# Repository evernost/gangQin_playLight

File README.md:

# PlayLight for gangQin
This repository contains the hardware design project for the LED light strip that goes with the gangQin app.

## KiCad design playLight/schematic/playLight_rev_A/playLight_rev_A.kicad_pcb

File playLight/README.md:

# PlayLight for gangQin

Custom piano light design.

---

## Overview

- **Type:** Amplifier
- **Domain:** Analog
- **Status:** Work in progress

---

## Features
TODO

---

## Interfaces

### Inputs
| Name | Type | Range | Description |
|-----|------|-------|-------------|
| IN | Audio | ±1V | Input signal |
| AMP_CV | Analog | 0–5 V | Volume control |

### Outputs
| Name | Type | Description |
|------|------|-------------|
| OUT | Audio | Filtered signal |

---

## Controls

| Control | Type | Description |
|--------|------|-------------|
| Cutoff | Potentiometer | Manual cutoff frequency |
| Resonance | Potentiometer | Feedback amount |

---

## Electrical Characteristics

- **Supply voltage:** ±12V
- **Current consumption:** TBD mA
- **Signal levels:** TBD

---

## Implementation Notes
Section is TODO.

---

## Files

| File | Description |
|-----|-------------|
| `headphones_amp_rev_A.pdf` | Electrical schematic (PDF export)|
| `headphones_amp_rev_A.kicad_pcb` | Schematic (KiCad 9.0.6)|
| `headphones_amp_rev_A.kicad_pcb` | PCB layout (KiCad 9.0.6)|
| `sim/XXX.asc` | SPICE simulation of the Schmitt Trigger |

---

## Calibration / Tuning
None.

---

## Known Issues / TODO
None.

---

## Revision History

| Revision | Date | Notes |
|--------|------|-------|
| Rev A | 2026-04-25 | Initial prototype without MCU |
| Rev B | YYYY-MM-DD | TBD |

---

## Tools
Designed with KiCAD 9.0.7

Designed on a 0.25mm grid (dimensions are driven by standard piano keyboard dimensions, which are in mm)
LED nets routed on a 0.20mm grid to avoid clearance issues when connecting to the LP5036.

---

## Related Modules

Links to other submodules in the repository:
- `../vca/`
- `../ring_modulator/`

---

## References
- TI datasheet: LP5036

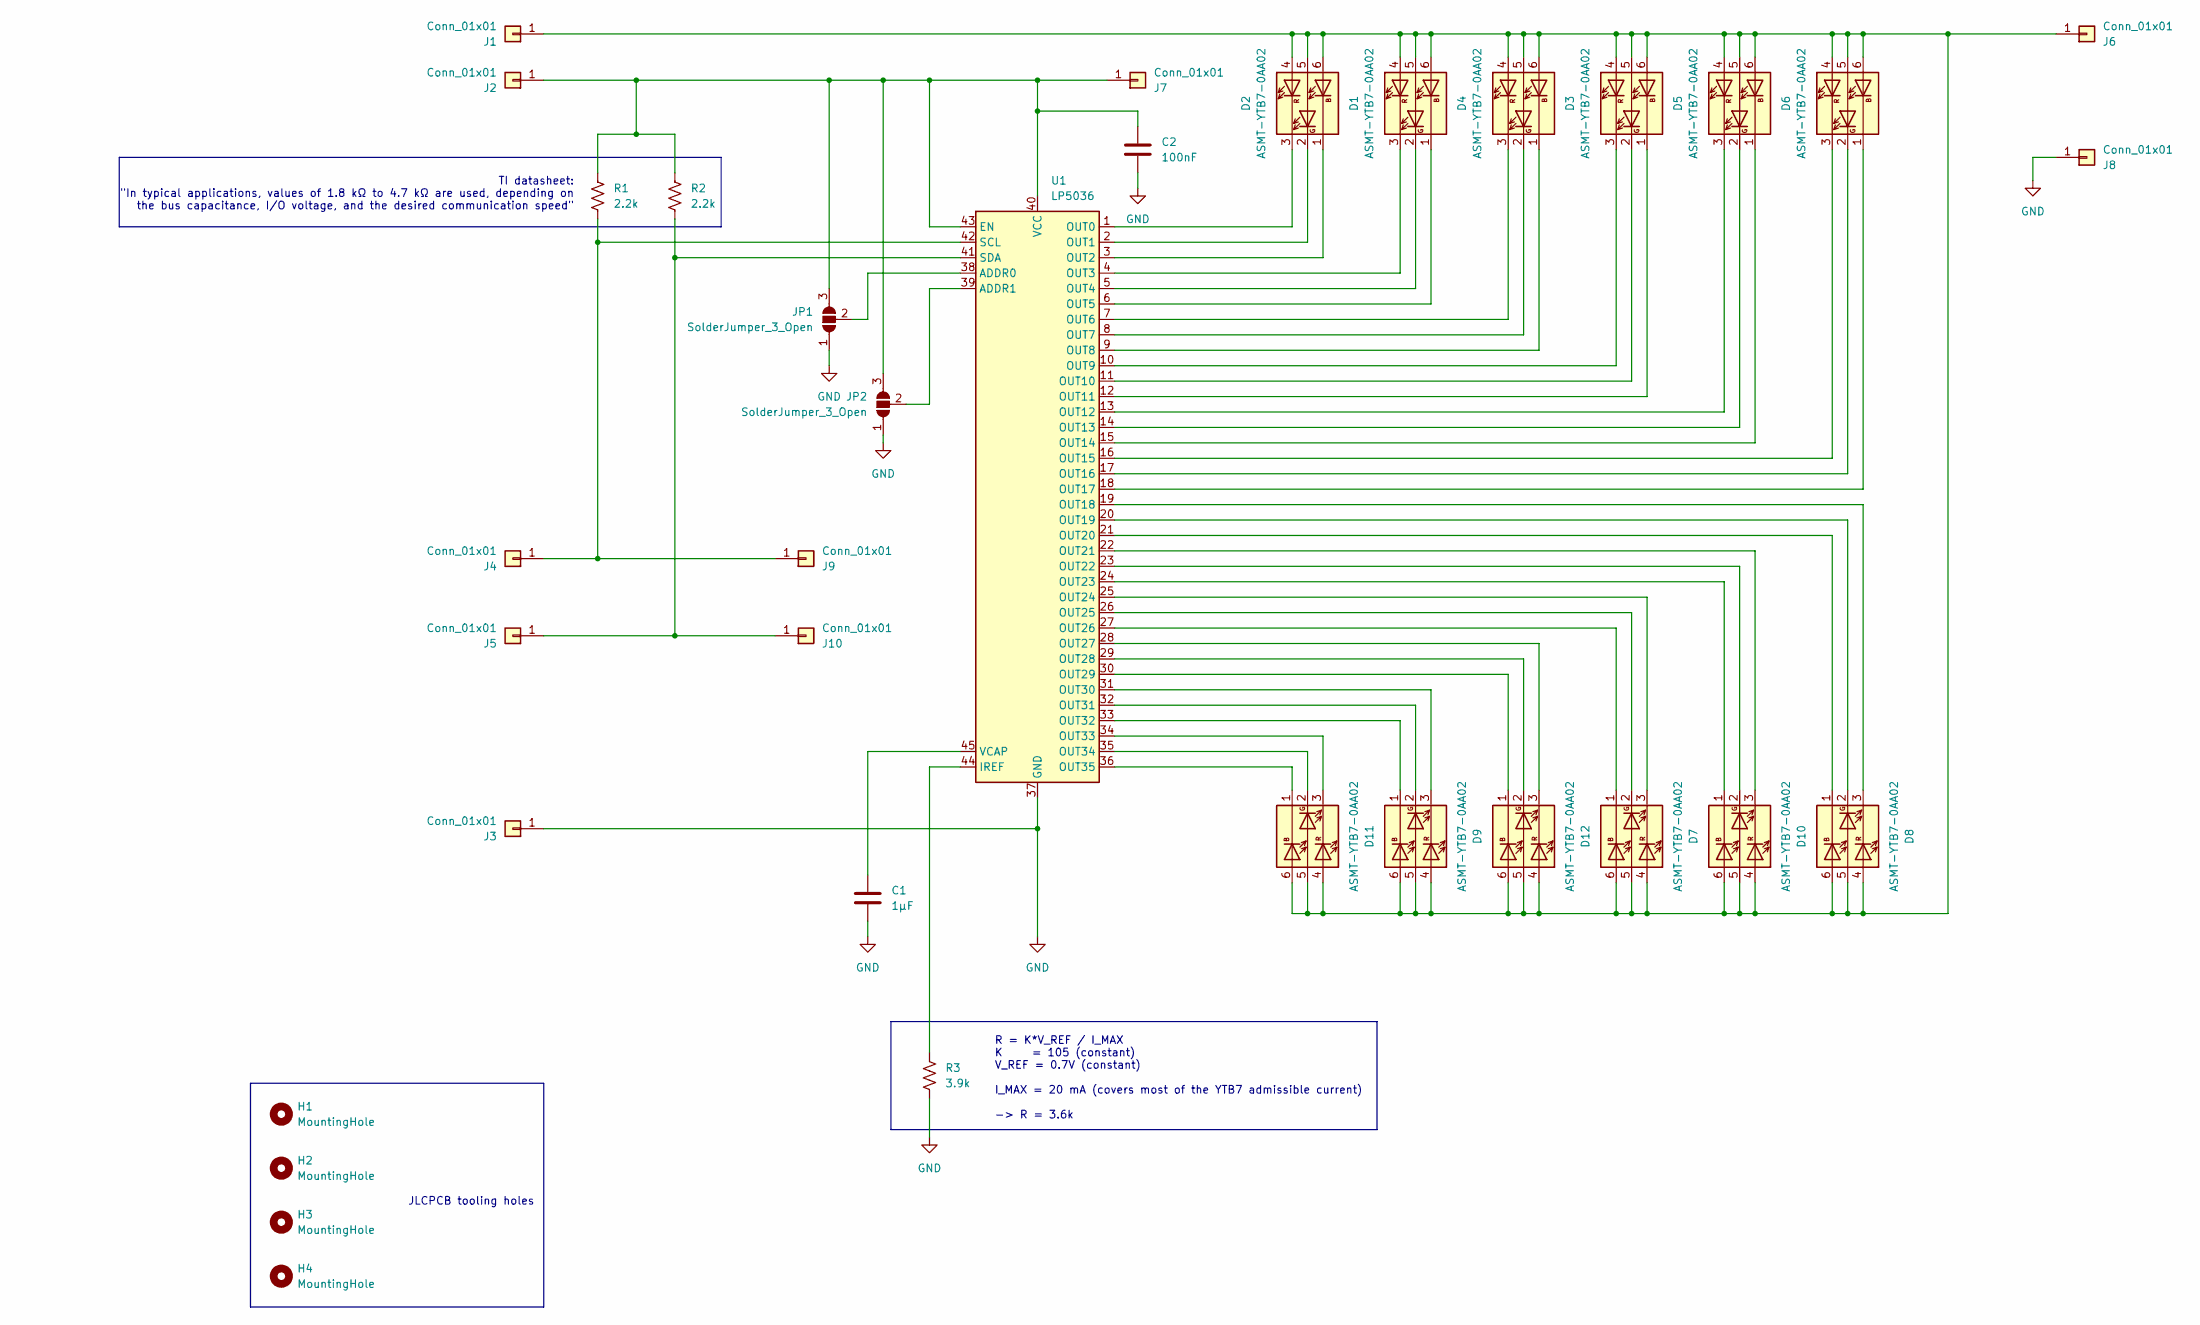
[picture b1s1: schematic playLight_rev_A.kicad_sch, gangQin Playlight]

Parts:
C1: 1µF; C_0805_2012Metric_Pad1.18x1.45mm_HandSolder; MPN C1712
C2: 100nF; C_0805_2012Metric_Pad1.18x1.45mm_HandSolder; MPN C1711
D1, D2, D3, D4, D5, D6, D7, D8, D9, D10, D11, D12: ASMT-YTB7-0AA02; LED_Avago_PLCC6_3x2.8mm; MPN C3018544
H1, H2, H3, H4: MountingHole; JLCPCB_Tooling_Hole
J1, J2, J3, J4, J5, J6, J7, J8, J9, J10: Conn_01x01; SolderWirePad_1x01_SMD_1.5x3mm
JP1, JP2: SolderJumper_3_Open; SolderJumper-3_P1.3mm_Open_RoundedPad1.0x1.5mm
R1, R2: 2.2k; R_0603_1608Metric_Pad0.98x0.95mm_HandSolder; MPN C4190
R3: 3.9k; R_0603_1608Metric_Pad0.98x0.95mm_HandSolder; MPN C23018
U1: LP5036; VQFN-46-1EP_5x6mm_P0.4mm_EP2.8x3.8mm; MPN C701961

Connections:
GND: C1.2, C2.2, J3.1, J8.1, JP1.1 (A), JP2.1 (A), R3.2, U1.37 (GND), U1.46 (GND), U1.47 (GND)
unnamed: D1.4 (AR), D1.5 (AG), D1.6 (AB), D2.4 (AR), D2.5 (AG), D2.6 (AB), D3.4 (AR), D3.5 (AG), D3.6 (AB), D4.4 (AR), D4.5 (AG), D4.6 (AB), D5.4 (AR), D5.5 (AG), D5.6 (AB), D6.4 (AR), D6.5 (AG), D6.6 (AB), D7.4 (AR), D7.5 (AG), D7.6 (AB), D8.4 (AR), D8.5 (AG), D8.6 (AB), D9.4 (AR), D9.5 (AG), D9.6 (AB), D10.4 (AR), D10.5 (AG), D10.6 (AB), D11.4 (AR), D11.5 (AG), D11.6 (AB), D12.4 (AR), D12.5 (AG), D12.6 (AB), J1.1, J6.1
unnamed: D1.1 (KB), U1.6 (OUT5)
unnamed: D1.2 (KG), U1.5 (OUT4)
unnamed: D1.3 (KR), U1.4 (OUT3)
unnamed: D2.1 (KB), U1.3 (OUT2)
unnamed: D2.2 (KG), U1.2 (OUT1)
unnamed: D2.3 (KR), U1.1 (OUT0)
unnamed: D3.1 (KB), U1.12 (OUT11)
unnamed: D3.2 (KG), U1.11 (OUT10)
unnamed: D3.3 (KR), U1.10 (OUT9)
unnamed: D4.1 (KB), U1.9 (OUT8)
unnamed: D4.2 (KG), U1.8 (OUT7)
unnamed: D4.3 (KR), U1.7 (OUT6)
unnamed: D5.1 (KB), U1.15 (OUT14)
unnamed: D5.2 (KG), U1.14 (OUT13)
unnamed: D5.3 (KR), U1.13 (OUT12)
unnamed: D6.1 (KB), U1.18 (OUT17)
unnamed: D6.2 (KG), U1.17 (OUT16)
unnamed: D6.3 (KR), U1.16 (OUT15)
unnamed: D7.1 (KB), U1.27 (OUT26)
unnamed: D7.2 (KG), U1.26 (OUT25)
unnamed: D7.3 (KR), U1.25 (OUT24)
unnamed: D8.1 (KB), U1.21 (OUT20)
unnamed: D8.2 (KG), U1.20 (OUT19)
unnamed: D8.3 (KR), U1.19 (OUT18)
unnamed: D9.1 (KB), U1.33 (OUT32)
unnamed: D9.2 (KG), U1.32 (OUT31)
unnamed: D9.3 (KR), U1.31 (OUT30)
unnamed: D10.1 (KB), U1.24 (OUT23)
unnamed: D10.2 (KG), U1.23 (OUT22)
unnamed: D10.3 (KR), U1.22 (OUT21)
unnamed: D11.1 (KB), U1.36 (OUT35)
unnamed: D11.2 (KG), U1.35 (OUT34)
unnamed: D11.3 (KR), U1.34 (OUT33)
unnamed: D12.1 (KB), U1.30 (OUT29)
unnamed: D12.2 (KG), U1.29 (OUT28)
unnamed: D12.3 (KR), U1.28 (OUT27)
unnamed: C2.1, J2.1, J7.1, JP1.3 (B), JP2.3 (B), R1.1, R2.1, U1.40 (VCC), U1.43 (EN)
unnamed: J4.1, J9.1, R1.2, U1.42 (SCL)
unnamed: J5.1, J10.1, R2.2, U1.41 (SDA)
unnamed: JP1.2 (C), U1.38 (ADDR0)
unnamed: JP2.2 (C), U1.39 (ADDR1)
unnamed: R3.1, U1.44 (IREF)
unnamed: C1.1, U1.45 (VCAP)

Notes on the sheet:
R = K*V_REF / I_MAX K = 105 (constant) V_REF = 0.7V (constant) I_MAX = 20 mA (covers most of the YTB7 admissible current) -> R = 3.6k
JLCPCB tooling holes
TI datasheet: "In typical applications, values of 1.8 kΩ to 4.7 kΩ are used, depending on the bus capacitance, I/O voltage, and the desired communication speed"

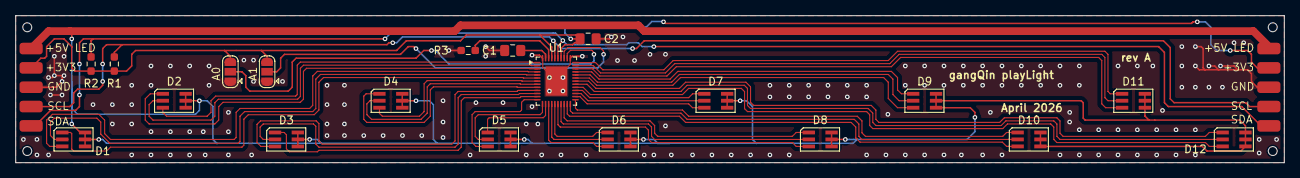
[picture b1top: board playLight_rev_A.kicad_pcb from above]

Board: 2 copper layers, 164.0 x 19.0 mm, 34 parts (0 on the bottom side), 45 nets.

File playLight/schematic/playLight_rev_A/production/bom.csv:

Designator,Footprint,Quantity,Value,LCSC Part #
C1,0805,1,1µF,C1712
C2,0805,1,100nF,C1711
"D1, D10, D11, D12, D2, D3, D4, D5, D6, D7, D8, D9",LED_Avago_PLCC6_3x2.8mm,12,ASMT-YTB7-0AA02,C3018544
"R1, R2",0603,2,2.2k,C4190
R3,0603,1,3.9k,C23018
U1,VQFN-46-1EP_5x6mm_P0.4mm_EP2.8x3.8mm,1,LP5036,C701961

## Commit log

2026-04-17 added kicad project
2026-04-17 added doc
2026-04-18 added first draft of the schematic added outline for the PCB and first placement of the LEDs
2026-04-18 added a few swaps to simplify routing
2026-04-19 added a simplified revision replaced MCU with a 2x I2C support
2026-04-19 finalised routing (without ground plane)
2026-04-20 added gerbers added PDF export
2026-04-21 added design notes in the schematic minor tweaks in the PCB generated the gerbers accordingly
2026-04-25 changed the LED routing to pass the DRC
2026-04-25 added the mounting holes required by JLCPCB
2026-04-25 removed J connectors from BOM added LCSC refs
2026-04-25 fixed a few LCSC references
